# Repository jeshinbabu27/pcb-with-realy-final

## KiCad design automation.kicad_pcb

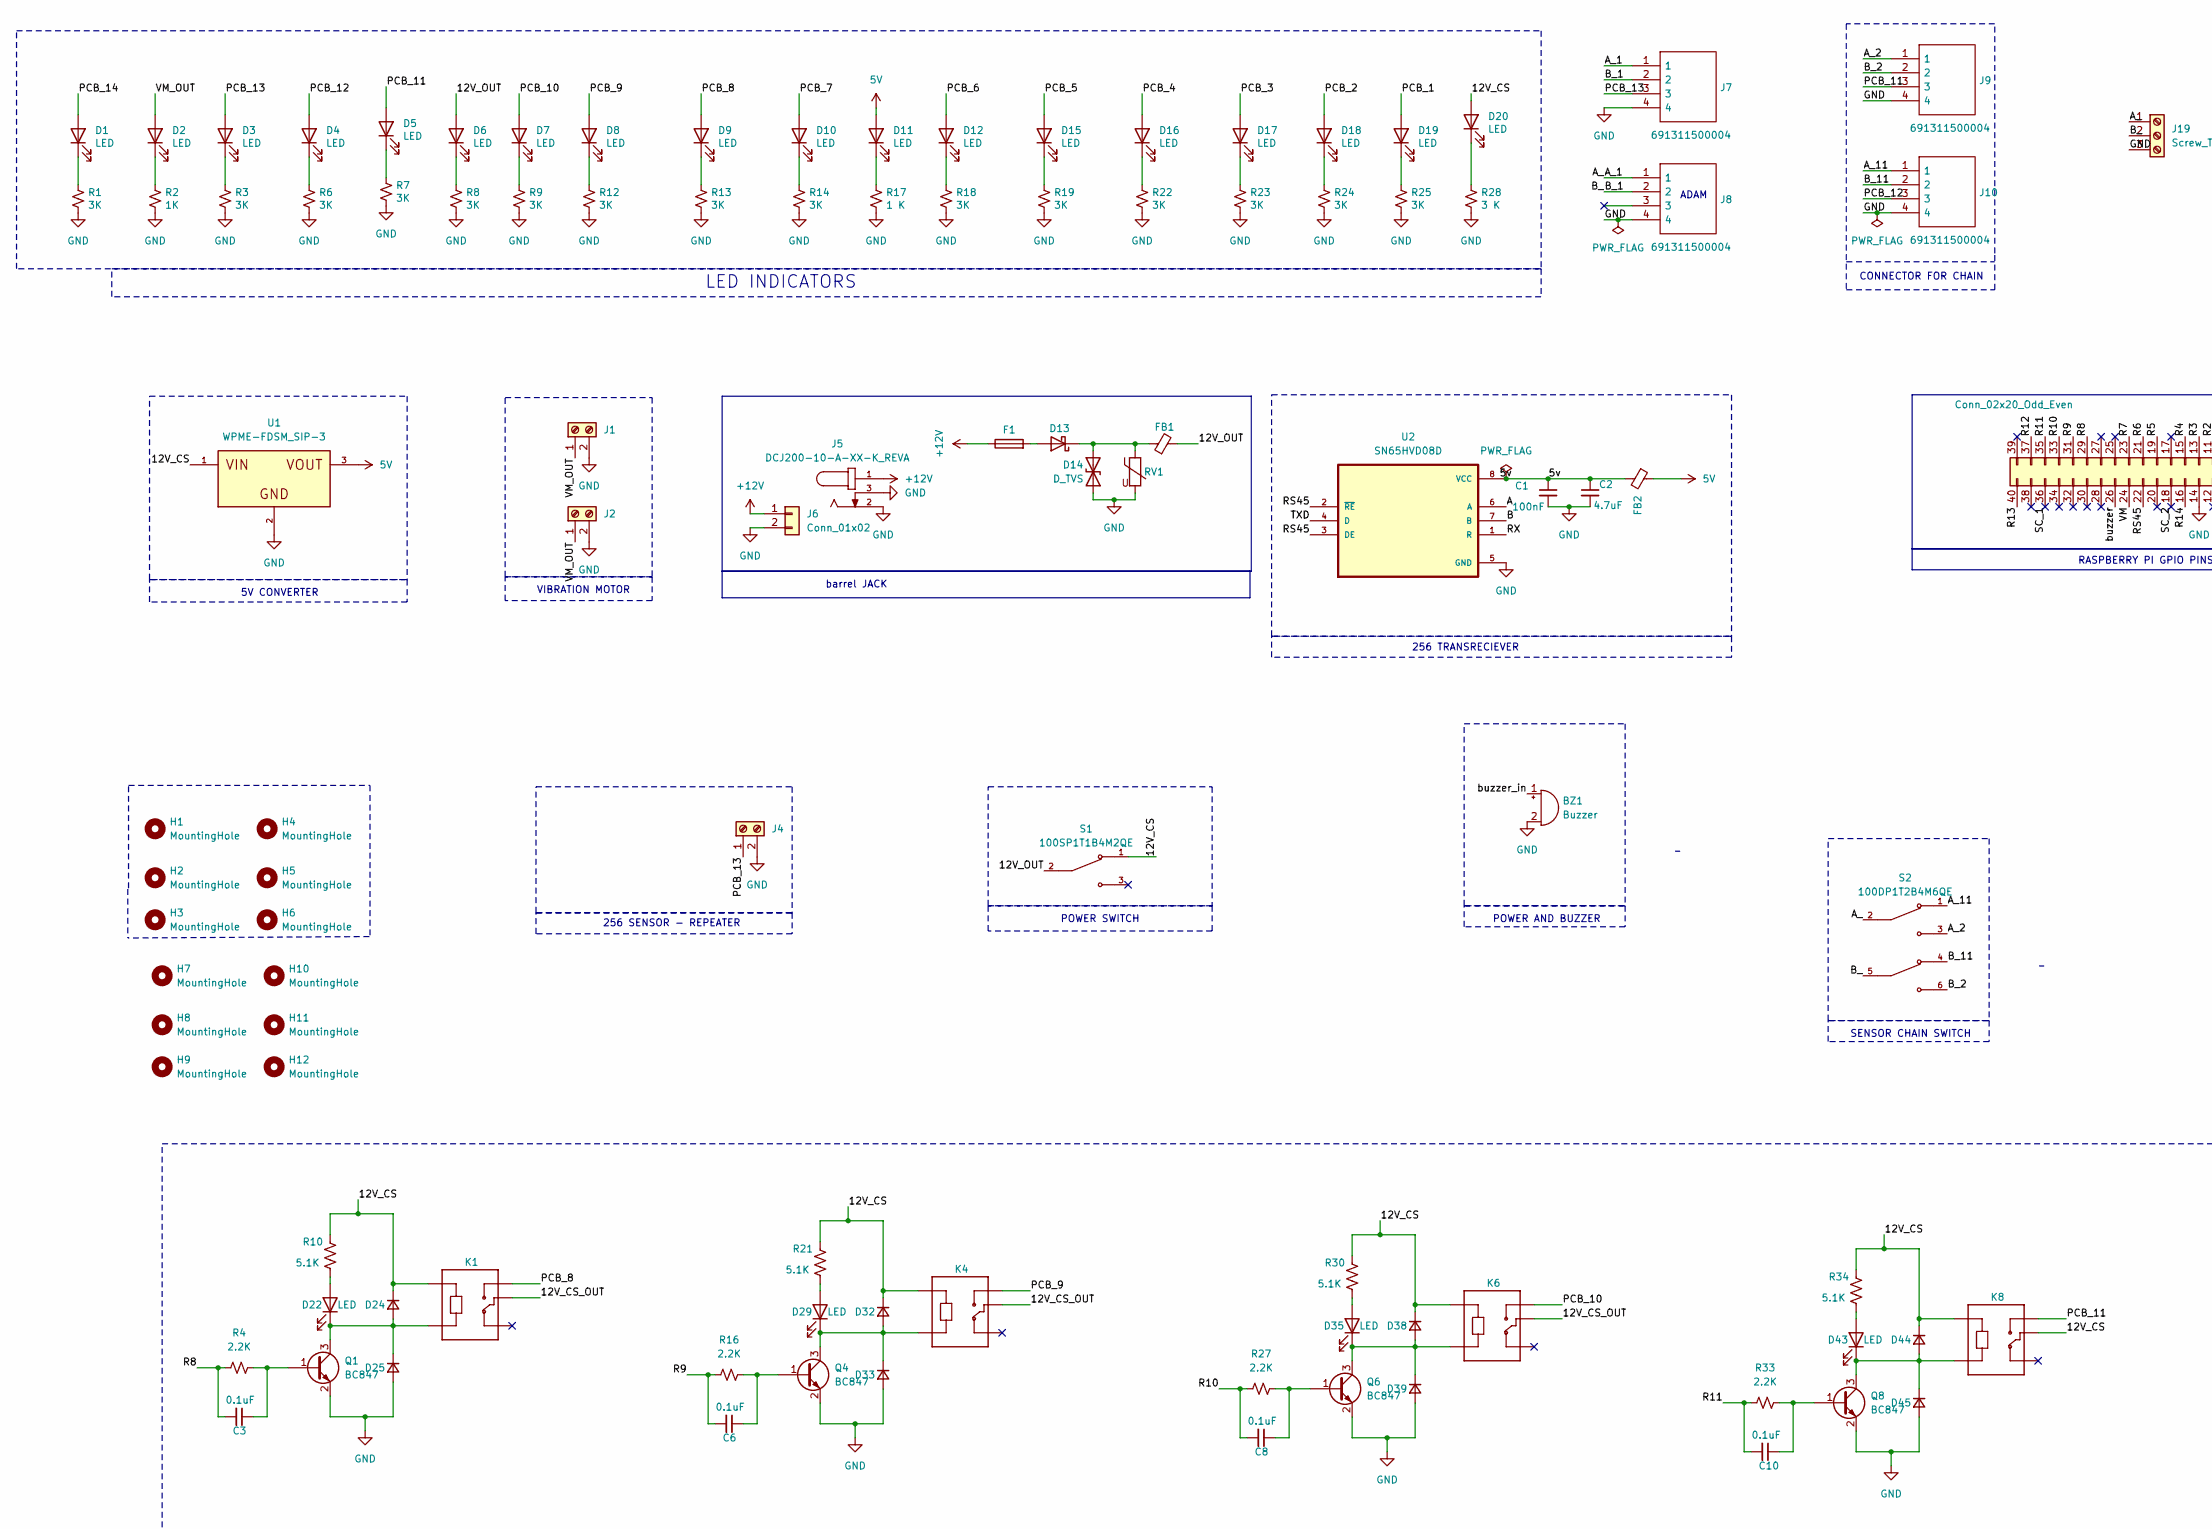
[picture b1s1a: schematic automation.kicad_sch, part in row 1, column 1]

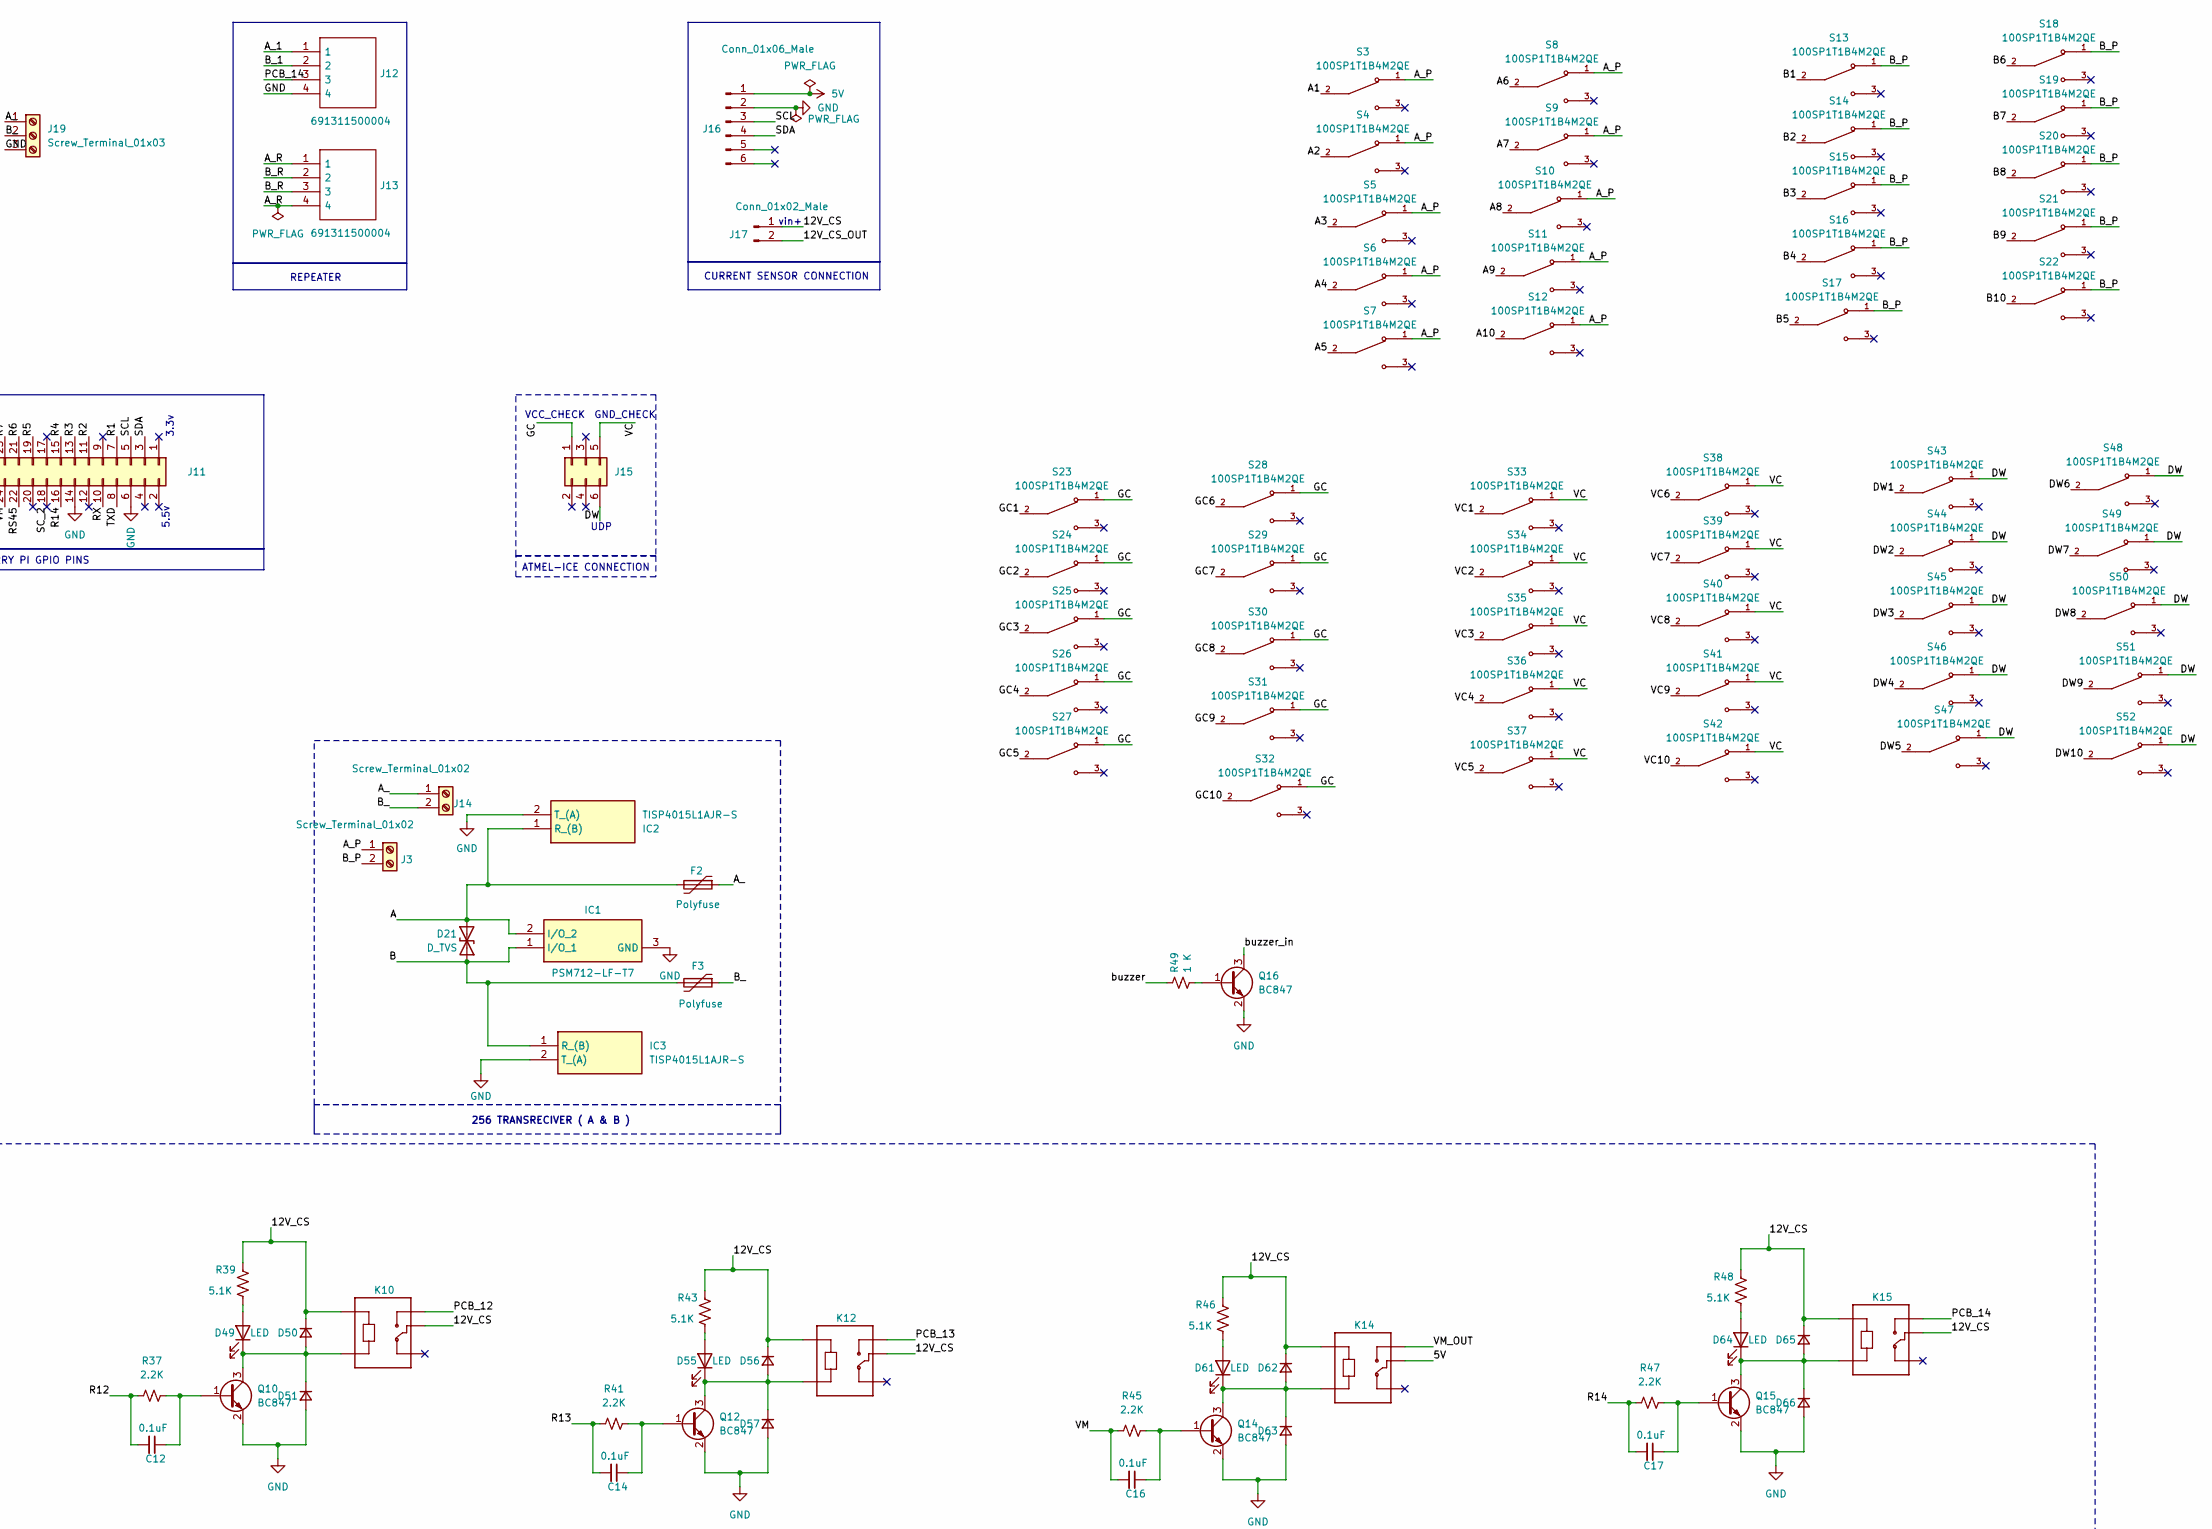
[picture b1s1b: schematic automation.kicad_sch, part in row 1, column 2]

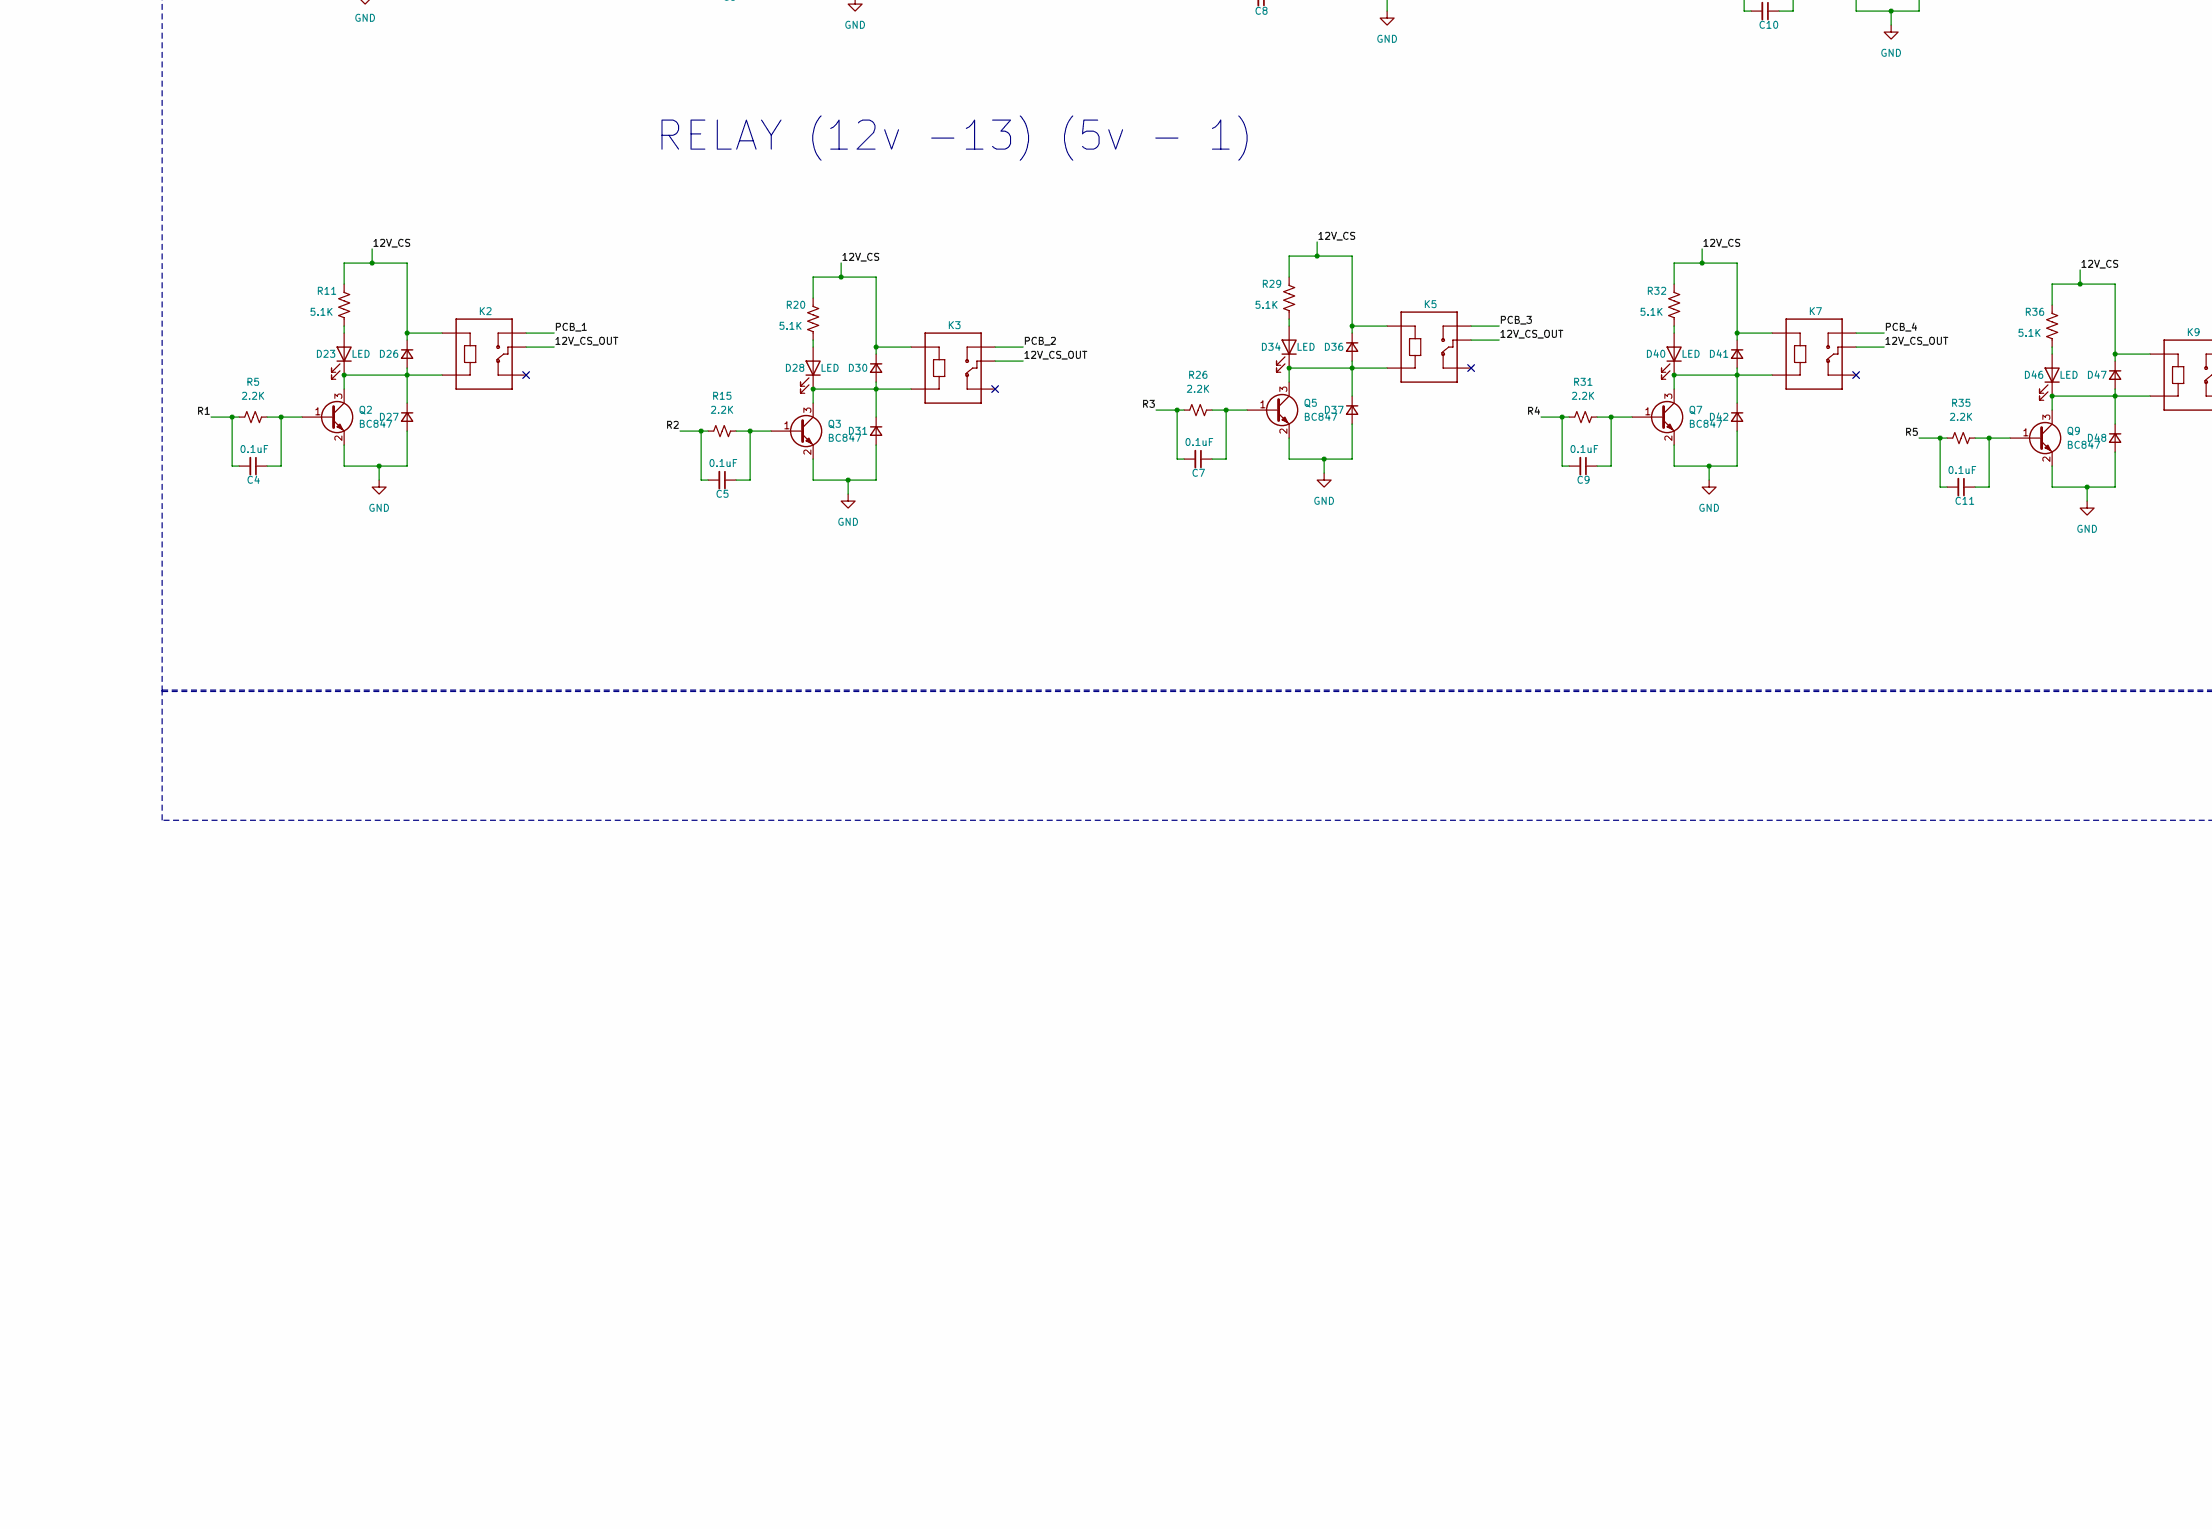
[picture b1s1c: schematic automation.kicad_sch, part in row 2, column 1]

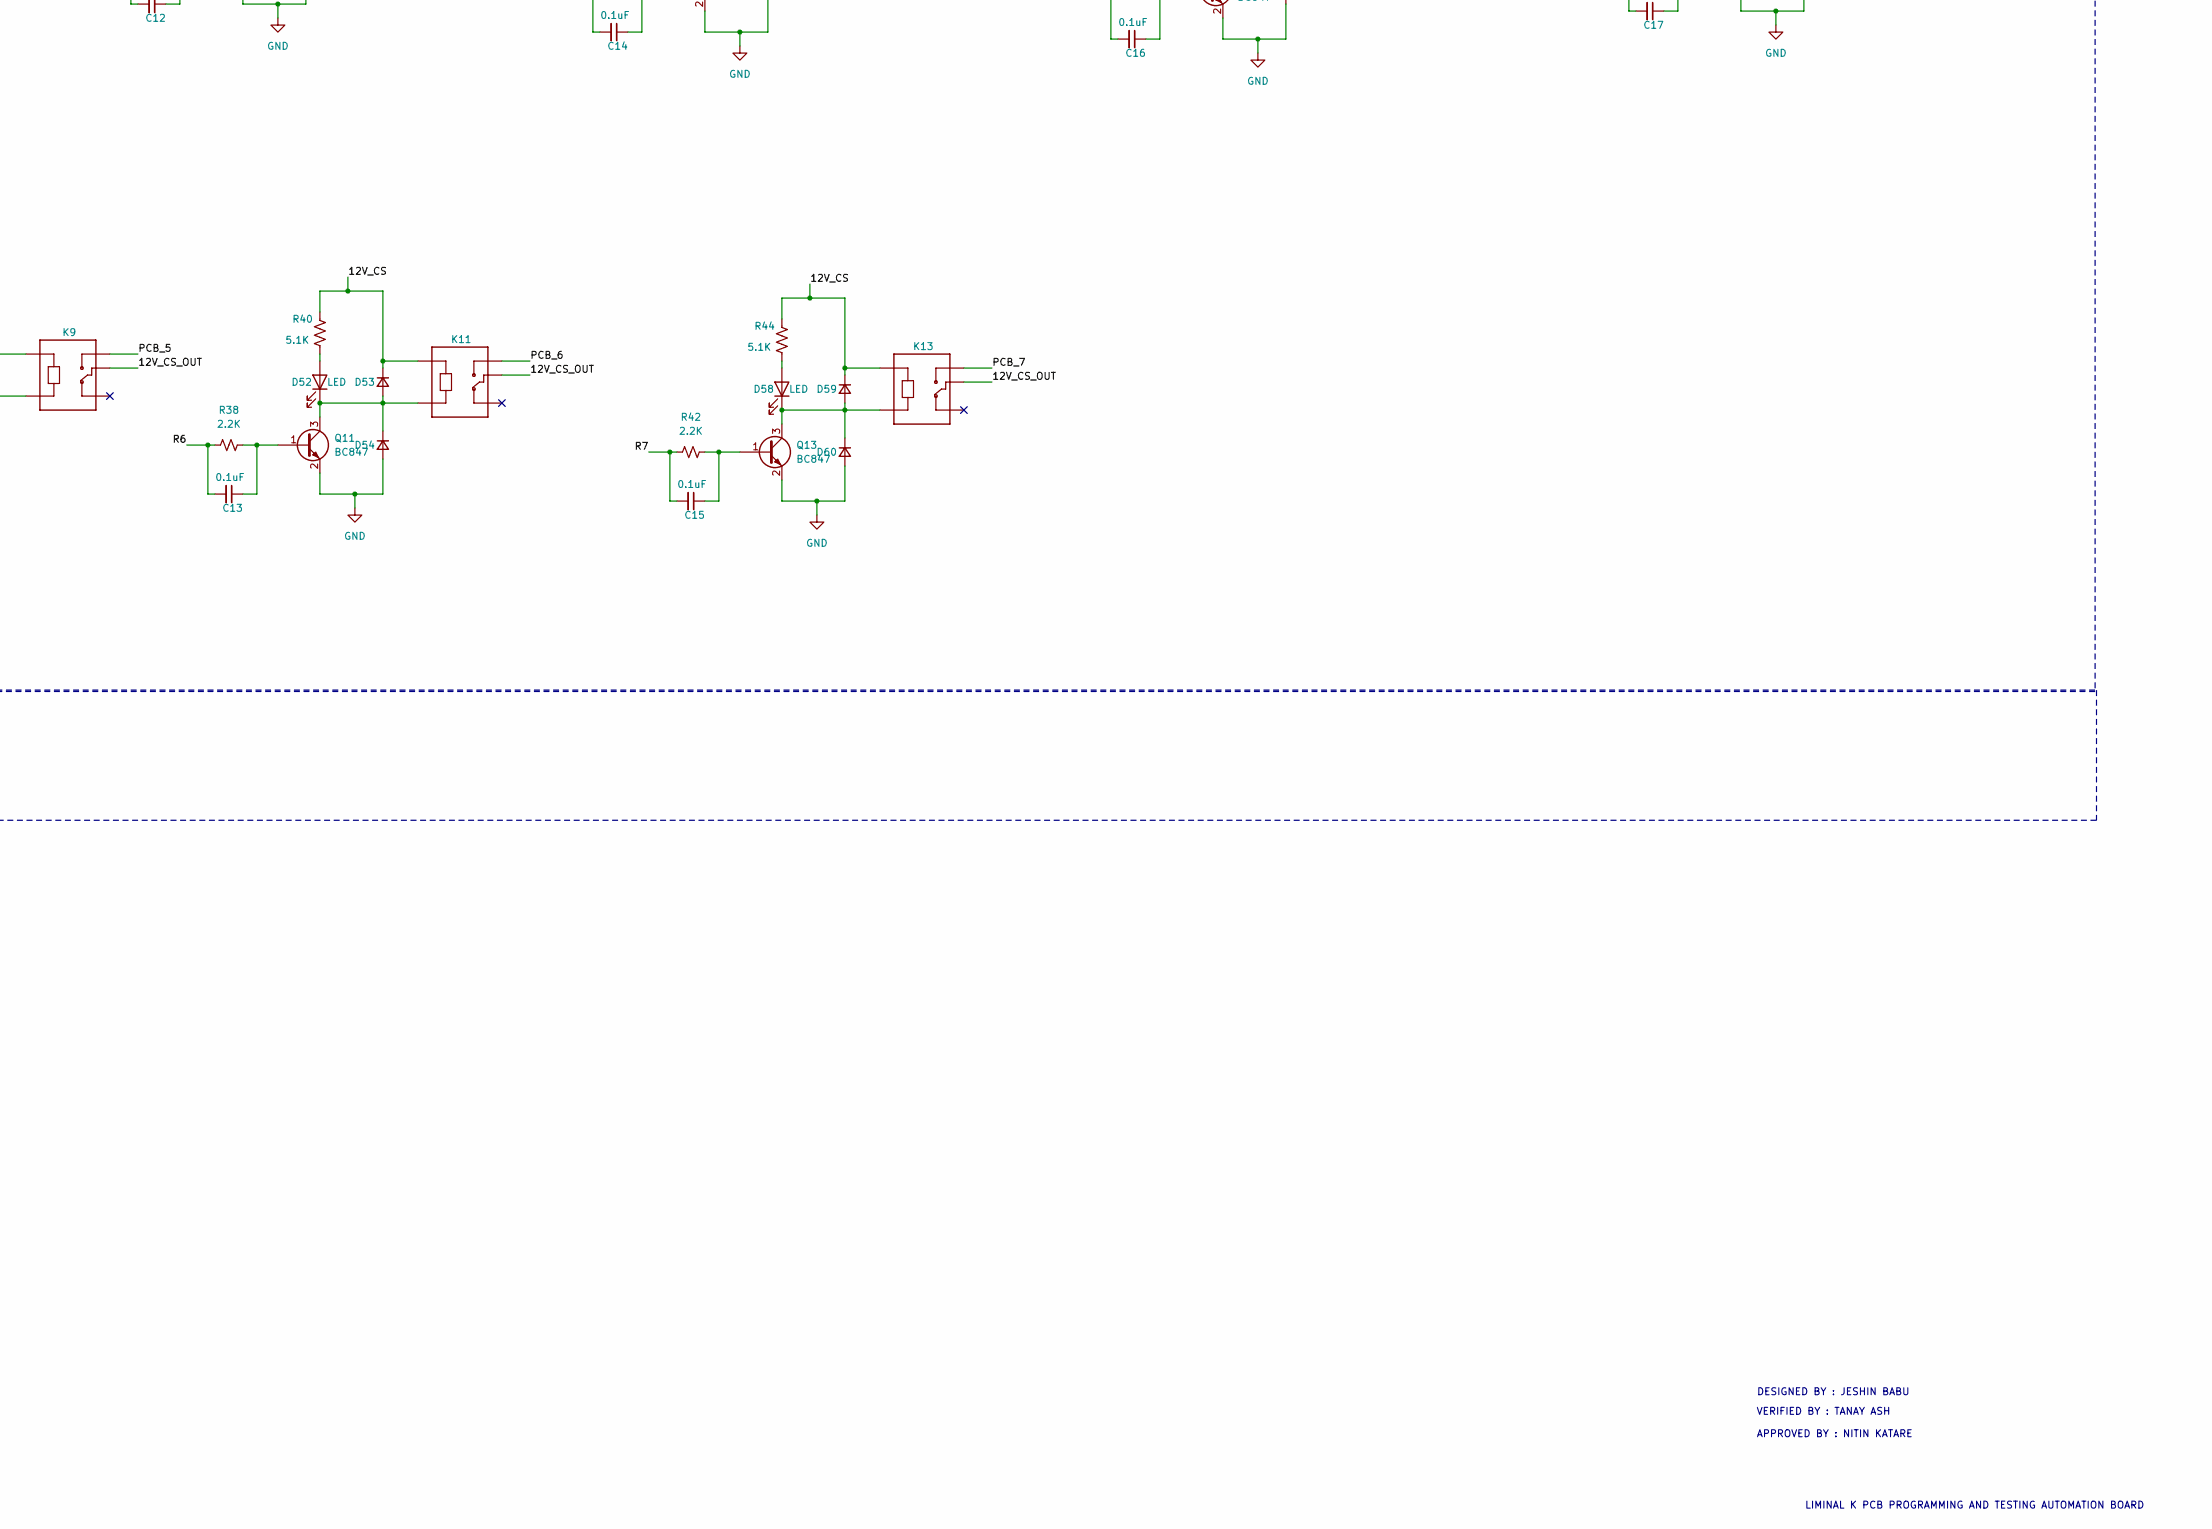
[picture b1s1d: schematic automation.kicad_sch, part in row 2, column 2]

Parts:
BZ1: Buzzer; MagneticBuzzer_StarMicronics_HMB-06_HMB-12
C1: 100nF; C_0805_2012Metric_Pad1.18x1.45mm_HandSolder
C2: 4.7uF; C_0805_2012Metric_Pad1.18x1.45mm_HandSolder
C3, C4, C5, C6, C7, C8, C9, C10, C11, C12, C13, C14, C15, C16, C17: 0.1uF; C_0603_1608Metric
D1, D2, D3, D4, D5, D6, D7, D8, D9, D10, D11, D12, D15, D16, D17, D18, D19, D20: LED; LED_1206_3216Metric_Pad1.42x1.75mm_HandSolder
D13: D_Schottky; D_SMA
D14: D_TVS; D_SMA
D21: D_TVS; D_SOD-123
D22, D23, D28, D29, D34, D35, D40, D43, D46, D49, D52, D55, D58, D61, D64: LED; LED_0805_2012Metric
D24, D25, D26, D27, D30, D31, D32, D33, D36, D37, D38, D39, D41, D42, D44, D45, D47, D48, D50, D51, D53, D54, D56, D57, D59, D60, D62, D63, D65, D66: D_Small; D_MELF
F1: Fuse; Fuse_0805_2012Metric_Pad1.15x1.40mm_HandSolder
F2, F3: Polyfuse; R_1206_3216Metric
FB1, FB2: FerriteBead_Small; R_0805_2012Metric_Pad1.20x1.40mm_HandSolder
H1, H2, H3, H4, H5, H6, H7, H8, H9, H10, H11, H12: MountingHole; MountingHole_3.2mm_M3_DIN965_Pad
IC1: PSM712-LF-T7; SOT-23-3; Manufacturer_Part_Number PSM712-LF-T7
IC2, IC3: TISP4015L1AJR-S; D_SMA; Manufacturer_Part_Number TISP4015L1AJR-S; Mouser Part Number 652-TISP4015L1AJR-S
J1, J2, J4: Screw_Terminal_01x02; 691311500002(2PIN)
J3, J14: Screw_Terminal_01x02; TerminalBlock_bornier-2_P5.08mm
J5: DCJ200-10-A-XX-K_REVA; GCT_DCJ200-10-A-XX-K_REVA; PARTREV A
J6: Conn_01x02; AMASS_XT60-M_1x02_P7.20mm_Vertical
J7, J8, J9, J10, J12, J13: 691311500004; Manufacturer_Part_Number 691311500004; Mouser Part Number 710-691311500004
J11: Conn_02x20_Odd_Even; PinSocket_2x20_P2.54mm_Vertical
J15: Conn_02x03_Odd_Even; IDC-Header_2x03_P2.54mm_Vertical
J16: Conn_01x06_Male; PinHeader_1x06_P2.54mm_Vertical
J17: Conn_01x02_Male; 691214110002
J19: Screw_Terminal_01x03; 691311500003(3pins)
K1, K2, K3, K4, K5, K6, K7, K8, K9, K10, K11, K12, K13, K14, K15: e; RELAY_SRD-05VDC-SL-C
Q1, Q2, Q3, Q4, Q5, Q6, Q7, Q8, Q9, Q10, Q11, Q12, Q13, Q14, Q15, Q16: BC847; SOT-23
R1, R3, R6, R7, R8, R9, R12, R13, R14, R18, R19, R22, R23, R24, R25: 3K; R_0603_1608Metric
R2: 1K; R_0603_1608Metric
R4, R5, R15, R16, R26, R27, R31, R33, R35, R37, R38, R41, R42, R45, R47: 2.2K; R_0603_1608Metric
R10, R11, R20, R21, R29, R30, R32, R34, R36, R39, R40, R43, R44, R46, R48: 5.1K; R_0603_1608Metric
R17, R49: 1 K; R_0603_1608Metric
R28: 3 K; R_0603_1608Metric
RV1: Varistor; R_0805_2012Metric
S1, S3, S4, S5, S6, S7, S8, S9, S10, S11, S12, S13, S14, S15, S16, S17, S18, S19, S20, S21, S22, S23, S24, S25, S26, S27, S28, S29, S30, S31, S32, S33, S34, S35, S36, S37, S38, S39, S40, S41, S42, S43, S44, S45, S46, S47, S48, S49, S50, S51, S52: 100SP1T1B4M2QE; SW_100SP1T1B4M2QE(SPST); PARTREV E
S2: 100DP1T2B4M6QE; SW_100DP1T2B4M6QE (DPDT); PARTREV G
U1: WPME-FDSM_SIP-3; WPME-FDSM_173010X78
U2: SN65HVD08D; SOIC127P599X175-8N5

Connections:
5V: D11.2 (A), FB2.1, J16.1, K14.COM, U1.3
+12V: F1.1, J5.1, J6.1
/5v: C1.1, C2.1, FB2.2, U2.8 (VCC)
/12V_CS: D20.2 (A), D24.1 (K), D26.1 (K), D30.1 (K), D32.1 (K), D36.1 (K), D38.1 (K), D41.1 (K), D44.1 (K), D47.1 (K), D50.1 (K), D53.1 (K), D56.1 (K), D59.1 (K), D62.1 (K), D65.1 (K), J17.1, K1.A1, K2.A1, K3.A1, K4.A1, K5.A1, K6.A1, K7.A1, K8.A1, K8.COM, K9.A1, K10.A1, K10.COM, K11.A1, K12.A1, K12.COM, K13.A1, K14.A1, K15.A1, K15.COM, R10.2, R11.2, R20.2, R21.2, R29.2, R30.2, R32.2, R34.2, R36.2, R39.2, R40.2, R43.2, R44.2, R46.2, R48.2, S1.1, U1.1
/12V_CS_OUT: J17.2, K1.COM, K2.COM, K3.COM, K4.COM, K5.COM, K6.COM, K7.COM, K9.COM, K11.COM, K13.COM
/12V_OUT: D6.2 (A), FB1.2, S1.2
/A: D21.2 (A2), F2.2, IC1.2 (I/O_2), IC2.1 (R_(B)), U2.6 (A)
/A1: S3.2
/A2: S4.2
/A3: S5.2
/A4: S6.2
/A5: S7.2
/A6: S8.2
/A7: S9.2
/A8: S10.2
/A9: S11.2
/A10: S12.2
/A_: F2.1, J7.1, J8.1, J12.1, J14.1, J19.1, S2.2
/A_2: J9.1, S2.3
/A_11: J10.1, S2.1
/A_P: J3.1, S3.1, S4.1, S5.1, S6.1, S7.1, S8.1, S9.1, S10.1, S11.1, S12.1
/A_R: J13.1, J13.4
/B: D21.1 (A1), F3.2, IC1.1 (I/O_1), IC3.1 (R_(B)), U2.7 (B)
/B1: S13.2
/B2: S14.2
/B3: S15.2
/B4: S16.2
/B5: S17.2
/B6: S18.2
/B7: S19.2
/B8: S20.2
/B9: S21.2
/B10: S22.2
/B_: F3.1, J7.2, J8.2, J12.2, J14.2, J19.2, S2.5
/B_2: J9.2, S2.6
/B_11: J10.2, S2.4
/B_P: J3.2, S13.1, S14.1, S15.1, S16.1, S17.1, S18.1, S19.1, S20.1, S21.1, S22.1
/B_R: J13.2, J13.3
/DW: J15.6, S43.1, S44.1, S45.1, S46.1, S47.1, S48.1, S49.1, S50.1, S51.1, S52.1
/DW1: S43.2
/DW2: S44.2
/DW3: S45.2
/DW4: S46.2
/DW5: S47.2
/DW6: S48.2
/DW7: S49.2
/DW8: S50.2
/DW9: S51.2
/DW10: S52.2
/GC: J15.1, S23.1, S24.1, S25.1, S26.1, S27.1, S28.1, S29.1, S30.1, S31.1, S32.1
/GC1: S23.2
/GC2: S24.2
/GC3: S25.2
/GC4: S26.2
/GC5: S27.2
/GC6: S28.2
/GC7: S29.2
/GC8: S30.2
/GC9: S31.2
/GC10: S32.2
/PCB_1: D19.2 (A), K2.NO
/PCB_2: D18.2 (A), K3.NO
/PCB_3: D17.2 (A), K5.NO
/PCB_4: D16.2 (A), K7.NO
/PCB_5: D15.2 (A), K9.NO
/PCB_6: D12.2 (A), K11.NO
/PCB_7: D10.2 (A), K13.NO
/PCB_8: D9.2 (A), K1.NO
/PCB_9: D8.2 (A), K4.NO
/PCB_10: D7.2 (A), K6.NO
/PCB_11: D5.2 (A), J9.3, K8.NO
/PCB_12: D4.2 (A), J10.3, K10.NO
/PCB_13: D3.2 (A), J4.1, J7.3, K12.NO
/PCB_14: D1.2 (A), J12.3, K15.NO
/R1: C4.2, J11.7, R5.1
/R2: C5.2, J11.11, R15.1
/R3: C7.2, J11.13, R26.1
/R4: C9.2, J11.15, R31.1
/R5: C11.2, J11.19, R35.1
/R6: C13.2, J11.21, R38.1
/R7: C15.2, J11.23, R42.1
/R8: C3.2, J11.29, R4.1
/R9: C6.2, J11.31, R16.1
/R10: C8.2, J11.33, R27.1
/R11: C10.2, J11.35, R33.1
/R12: C12.2, J11.37, R37.1
/R13: C14.2, J11.40, R41.1
/R14: C17.2, J11.16, R47.1
/RS45: J11.22, U2.2 (~RE), U2.3 (DE)
/RX: J11.10, U2.1 (R)
/SCL: J11.5, J16.3
/SC_1: J11.36
/SC_2: J11.18
/SDA: J11.3, J16.4
/TXD: J11.8, U2.4 (D)
/VC: J15.5, S33.1, S34.1, S35.1, S36.1, S37.1, S38.1, S39.1, S40.1, S41.1, S42.1
/VC1: S33.2
/VC2: S34.2
/VC3: S35.2
/VC4: S36.2
/VC5: S37.2
/VC6: S38.2
/VC7: S39.2
/VC8: S40.2
/VC9: S41.2
/VC10: S42.2
/VM: C16.2, J11.24, R45.1
/VM_OUT: D2.2 (A), J1.1, J2.1, K14.NO
/buzzer: J11.26, R49.1
/buzzer_in: BZ1.1 (+), Q16.3 (C)
GND: BZ1.2 (-), C1.2, C2.2, D14.1 (A1), D25.2 (A), D27.2 (A), D31.2 (A), D33.2 (A), D37.2 (A), D39.2 (A), D42.2 (A), D45.2 (A), D48.2 (A), D51.2 (A), D54.2 (A), D57.2 (A), D60.2 (A), D63.2 (A), D66.2 (A), IC1.3 (GND), IC2.2 (T_(A)), IC3.2 (T_(A)), J1.2, J2.2, J4.2, J5.2, J5.3, J6.2, J7.4, J8.4, J9.4, J10.4, J11.6, J11.14, J12.4, J16.2, J19.3, Q1.2 (E), Q2.2 (E), Q3.2 (E), Q4.2 (E), Q5.2 (E), Q6.2 (E), Q7.2 (E), Q8.2 (E), Q9.2 (E), Q10.2 (E), Q11.2 (E), Q12.2 (E), Q13.2 (E), Q14.2 (E), Q15.2 (E), Q16.2 (E), R1.2, R2.2, R3.2, R6.2, R7.2, R8.2, R9.2, R12.2, R13.2, R14.2, R17.2, R18.2, R19.2, R22.2, R23.2, R24.2, R25.2, R28.2, RV1.2, U1.2, U2.5 (GND)
unnamed: D1.1 (K), R1.1
unnamed: D2.1 (K), R2.1
unnamed: D3.1 (K), R3.1
unnamed: D4.1 (K), R6.1
unnamed: D5.1 (K), R7.1
unnamed: D6.1 (K), R8.1
unnamed: D7.1 (K), R9.1
unnamed: D8.1 (K), R12.1
unnamed: D9.1 (K), R13.1
unnamed: D10.1 (K), R14.1
unnamed: D11.1 (K), R17.1
unnamed: D12.1 (K), R18.1
unnamed: D13.2 (A), F1.2
unnamed: D13.1 (K), D14.2 (A2), FB1.1, RV1.1
unnamed: D15.1 (K), R19.1
unnamed: D16.1 (K), R22.1
unnamed: D17.1 (K), R23.1
unnamed: D18.1 (K), R24.1
unnamed: D19.1 (K), R25.1
unnamed: D20.1 (K), R28.1
unnamed: D22.2 (A), R10.1
unnamed: D22.1 (K), D24.2 (A), D25.1 (K), K1.A2, Q1.3 (C)
unnamed: D23.2 (A), R11.1
unnamed: D23.1 (K), D26.2 (A), D27.1 (K), K2.A2, Q2.3 (C)
unnamed: D28.2 (A), R20.1
unnamed: D28.1 (K), D30.2 (A), D31.1 (K), K3.A2, Q3.3 (C)
unnamed: D29.2 (A), R21.1
unnamed: D29.1 (K), D32.2 (A), D33.1 (K), K4.A2, Q4.3 (C)
unnamed: D34.2 (A), R29.1
unnamed: D34.1 (K), D36.2 (A), D37.1 (K), K5.A2, Q5.3 (C)
unnamed: D35.2 (A), R30.1
unnamed: D35.1 (K), D38.2 (A), D39.1 (K), K6.A2, Q6.3 (C)
unnamed: D40.2 (A), R32.1
unnamed: D40.1 (K), D41.2 (A), D42.1 (K), K7.A2, Q7.3 (C)
unnamed: D43.2 (A), R34.1
unnamed: D43.1 (K), D44.2 (A), D45.1 (K), K8.A2, Q8.3 (C)
unnamed: D46.2 (A), R36.1
unnamed: D46.1 (K), D47.2 (A), D48.1 (K), K9.A2, Q9.3 (C)
unnamed: D49.2 (A), R39.1
unnamed: D49.1 (K), D50.2 (A), D51.1 (K), K10.A2, Q10.3 (C)
unnamed: D52.2 (A), R40.1
unnamed: D52.1 (K), D53.2 (A), D54.1 (K), K11.A2, Q11.3 (C)
unnamed: D55.2 (A), R43.1
unnamed: D55.1 (K), D56.2 (A), D57.1 (K), K12.A2, Q12.3 (C)
unnamed: D58.2 (A), R44.1
unnamed: D58.1 (K), D59.2 (A), D60.1 (K), K13.A2, Q13.3 (C)
unnamed: D61.2 (A), R46.1
unnamed: D61.1 (K), D62.2 (A), D63.1 (K), K14.A2, Q14.3 (C)
unnamed: D64.2 (A), R48.1
unnamed: D64.1 (K), D65.2 (A), D66.1 (K), K15.A2, Q15.3 (C)
unnamed: C3.1, Q1.1 (B), R4.2
unnamed: C4.1, Q2.1 (B), R5.2
unnamed: C5.1, Q3.1 (B), R15.2
unnamed: C6.1, Q4.1 (B), R16.2
unnamed: C7.1, Q5.1 (B), R26.2
unnamed: C8.1, Q6.1 (B), R27.2
unnamed: C9.1, Q7.1 (B), R31.2
unnamed: C10.1, Q8.1 (B), R33.2
unnamed: C11.1, Q9.1 (B), R35.2
unnamed: C12.1, Q10.1 (B), R37.2
unnamed: C13.1, Q11.1 (B), R38.2
unnamed: C14.1, Q12.1 (B), R41.2
unnamed: C15.1, Q13.1 (B), R42.2
unnamed: C16.1, Q14.1 (B), R45.2
unnamed: C17.1, Q15.1 (B), R47.2
unnamed: Q16.1 (B), R49.2

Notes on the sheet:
ADAM
3.3v
VERIFIED BY : TANAY ASH
RELAY (12v -13) (5v - 1)
256 TRANSRECIEVER
DESIGNED BY : JESHIN BABU
vin+
GND_CHECK
POWER AND BUZZER
CURRENT SENSOR CONNECTION
REPEATER
ATMEL-ICE CONNECTION
256 TRANSRECIVER ( A & B )
UDP
VIBRATION MOTOR
5V CONVERTER
SENSOR CHAIN SWITCH
CONNECTOR FOR CHAIN
RASPBERRY PI GPIO PINS
VCC_CHECK
5.5v
POWER SWITCH
LED INDICATORS
256 SENSOR - REPEATER
LIMINAL K PCB PROGRAMMING AND TESTING AUTOMATION BOARD
barrel JACK
APPROVED BY : NITIN KATARE

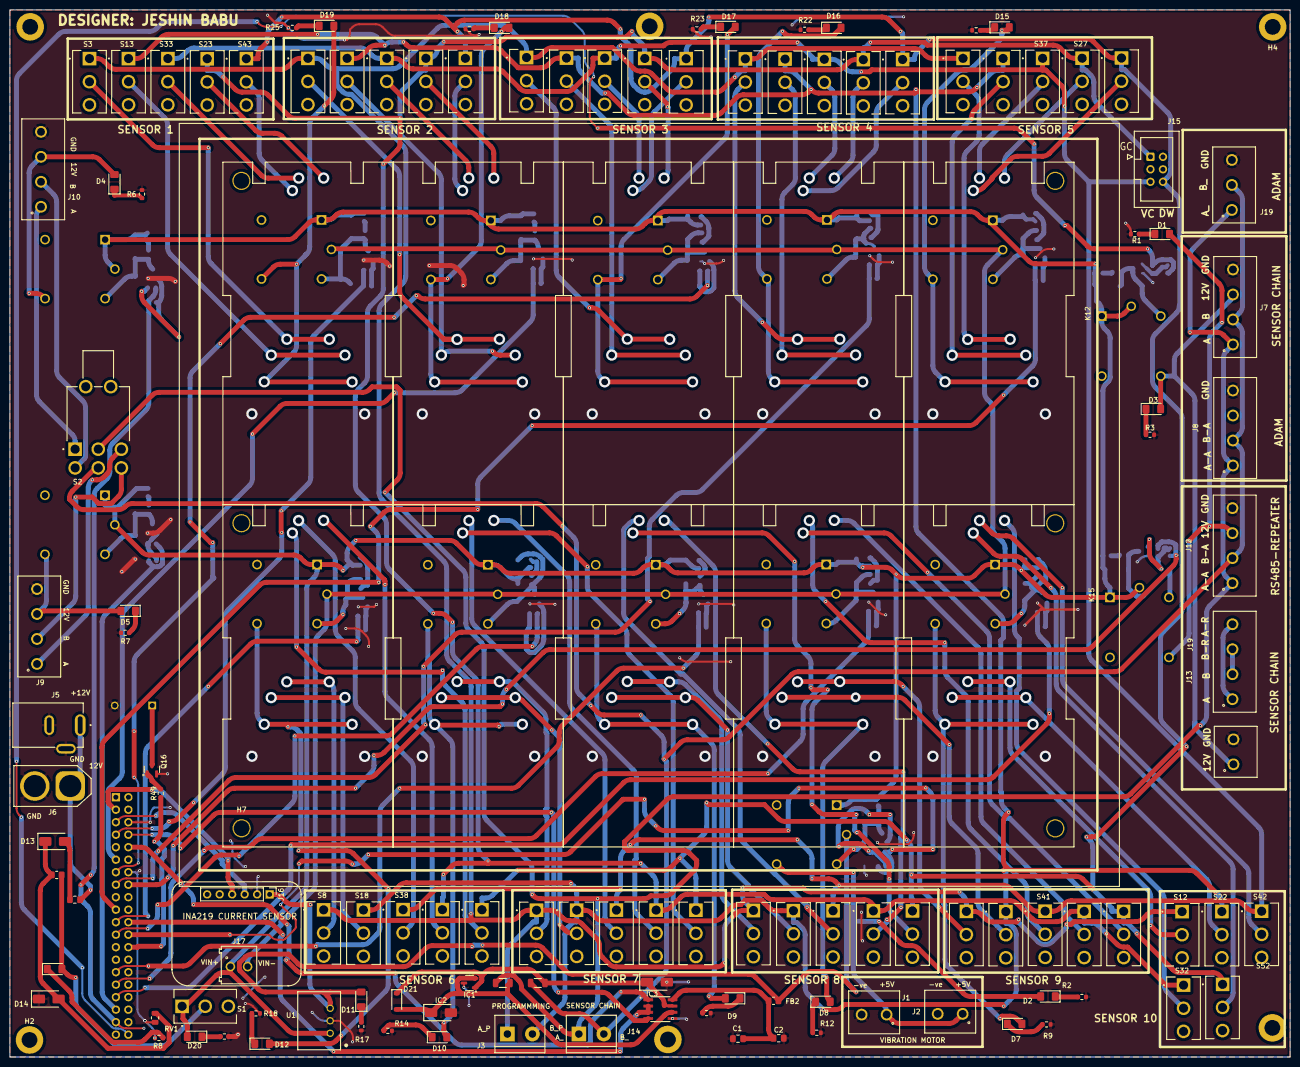
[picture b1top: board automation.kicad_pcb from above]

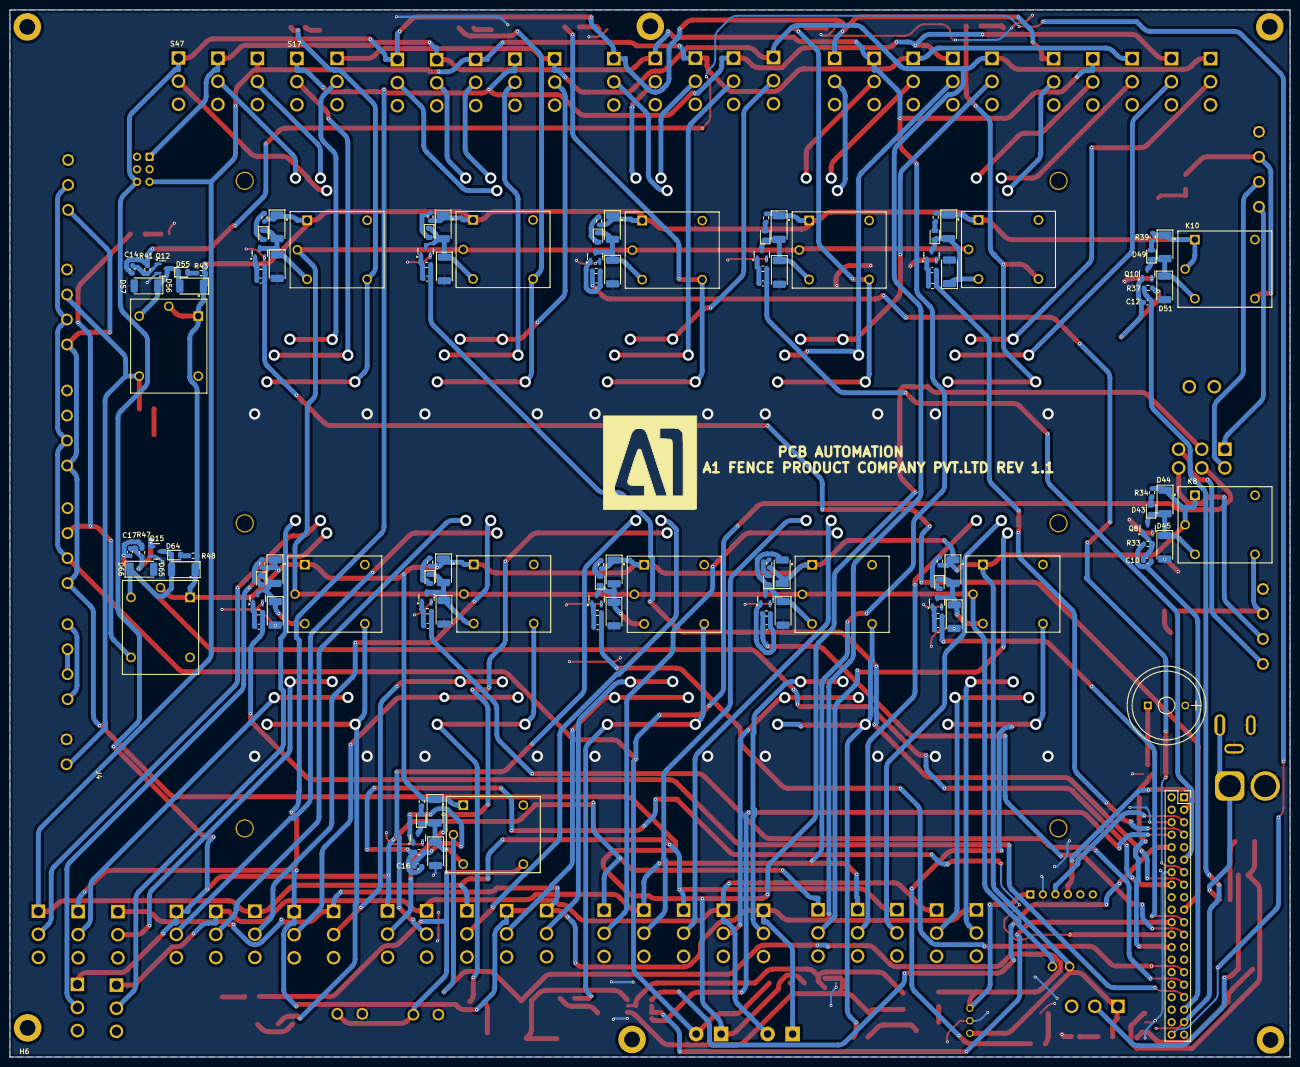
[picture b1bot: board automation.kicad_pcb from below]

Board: 14 copper layers, 260.2 x 212.8 mm, 257 parts (122 on the bottom side), 125 nets.
